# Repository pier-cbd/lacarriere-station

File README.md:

# Lacarriere Station 

## Specs
### Stage 1
- Powered by a battery recharged by a solar panel
- Three VGA cameras to take 360° photos
- Measures temperature/humidity/pressure with Bosch sensors
- Sends data via 2G+ network

### Stage 2
...

### Stage 3
...

## Sofwares
- KiCAD 7
- FreeCAD 0.20

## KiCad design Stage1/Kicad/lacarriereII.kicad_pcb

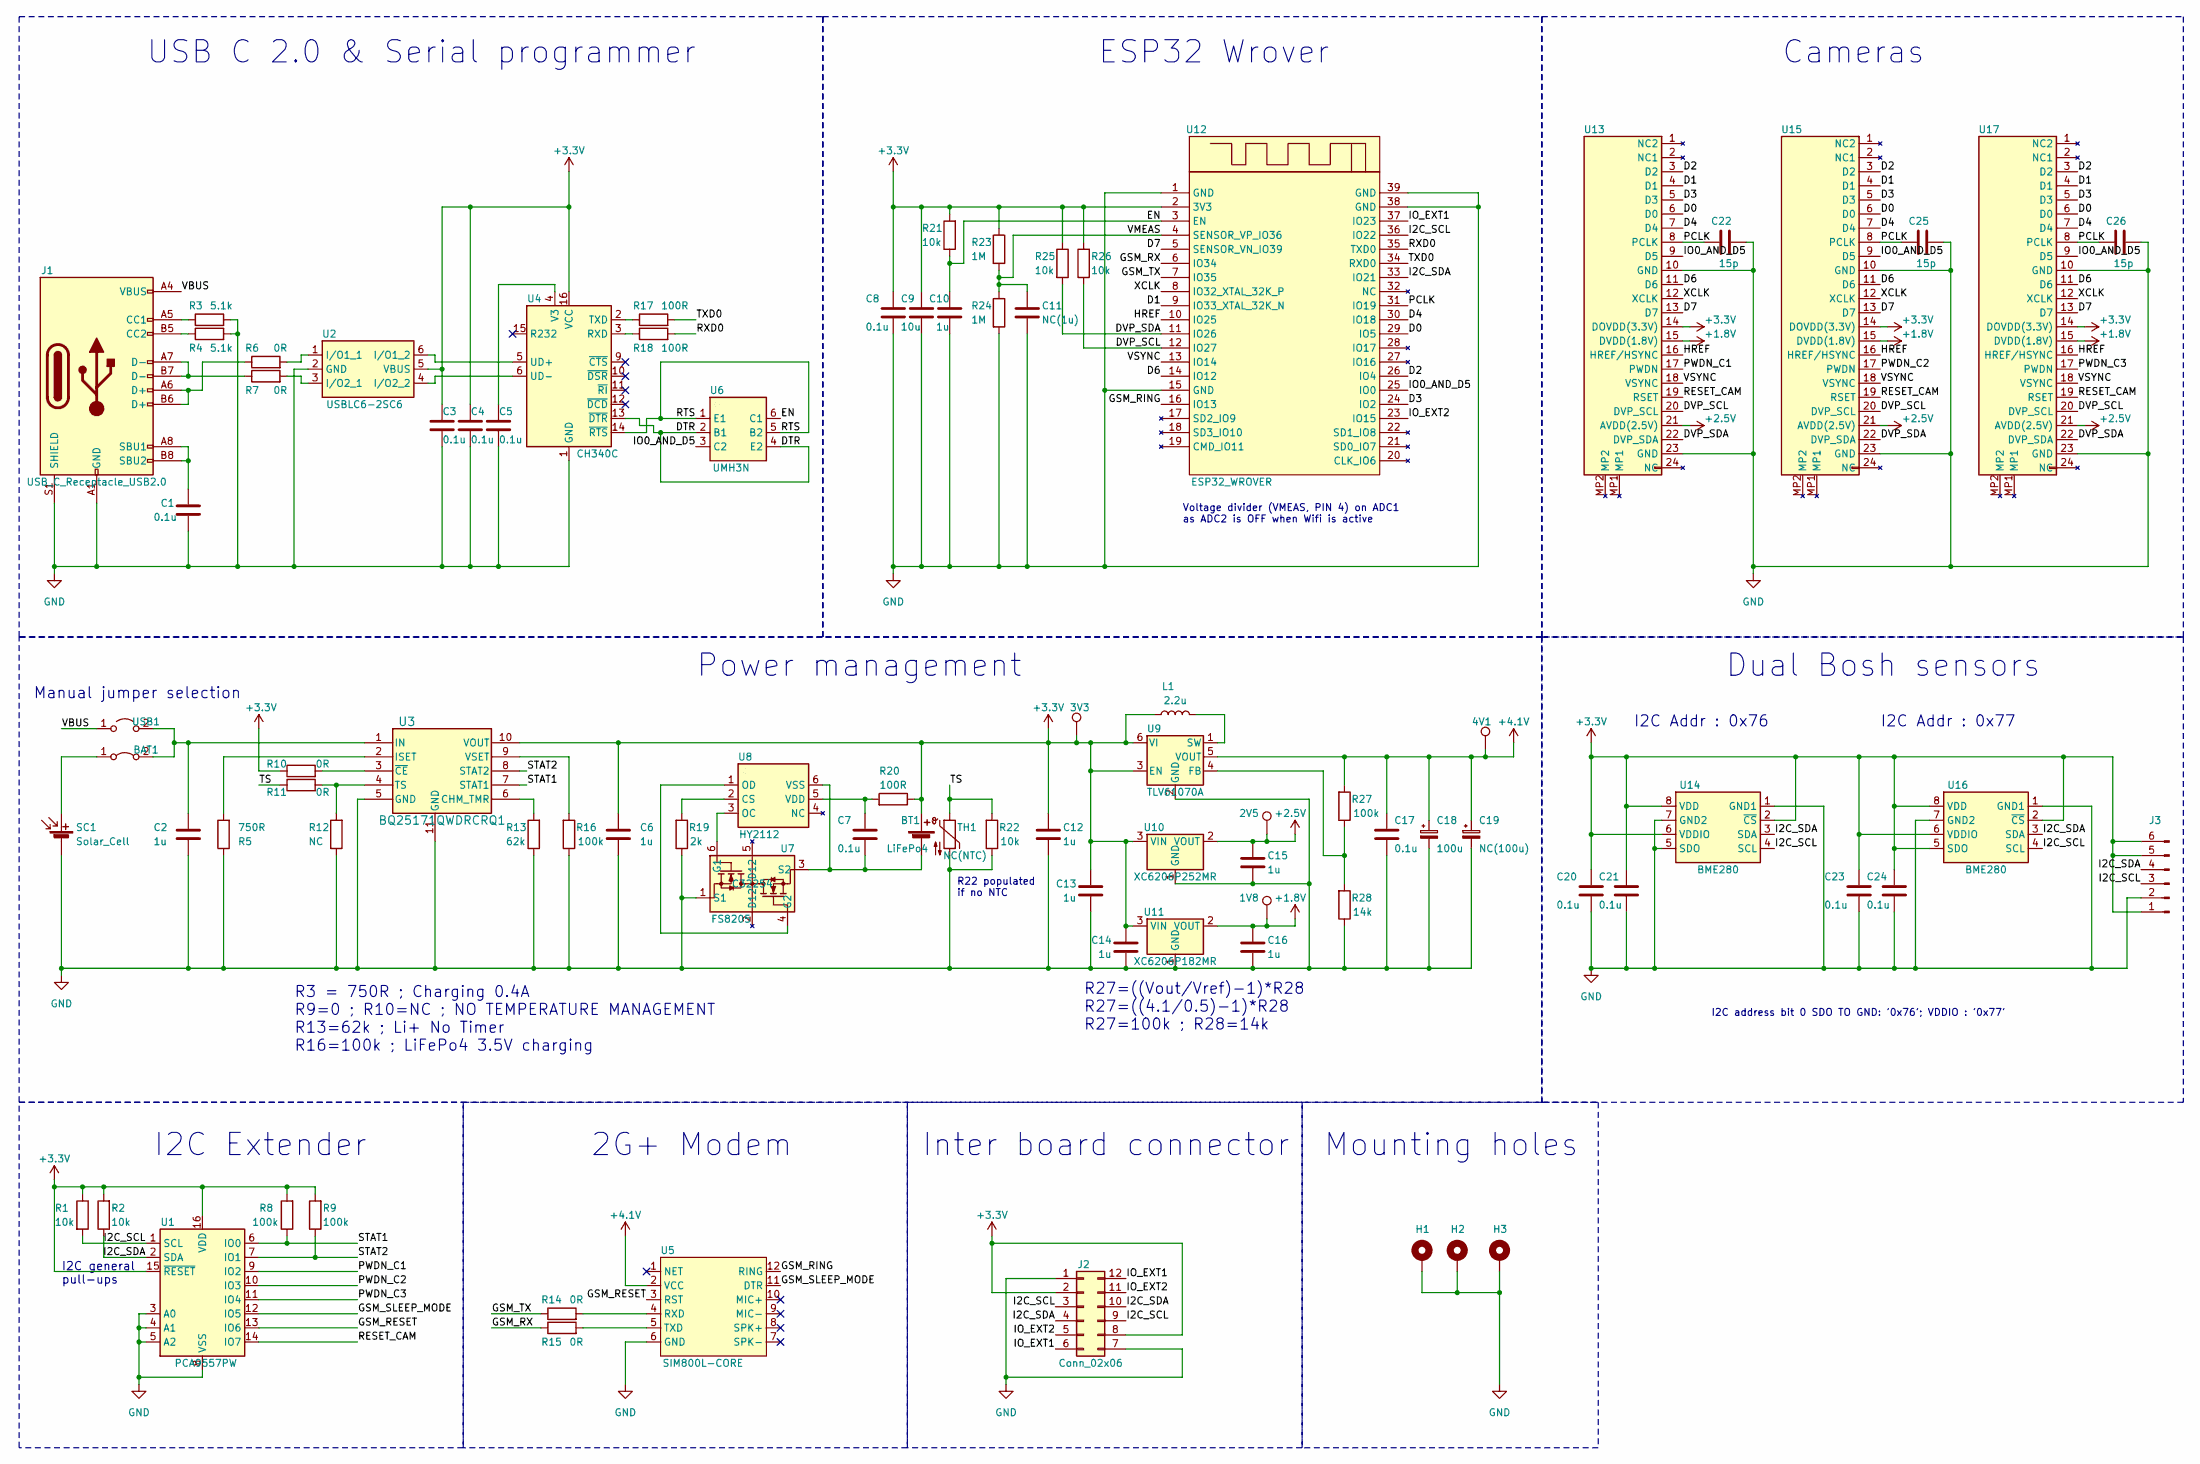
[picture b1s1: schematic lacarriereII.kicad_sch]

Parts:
1V8, 2V5, 3V3, 4V1: TestPoint; TestPoint_Pad_D1.5mm
BAT1: Jumper_2_Bridged; PinSocket_1x02_P2.54mm_Vertical_SMD_Pin1Right
BT1: LiFePo4; SolderWire-2.5sqmm_1x02_P8.8mm_D2.4mm_OD4.4mm
C1, C3, C4, C5, C7, C8, C17, C20, C21, C23, C24: 0.1u; C_0805_2012Metric_Pad1.18x1.45mm_HandSolder; LCSC C1711
C2, C6, C10, C12, C13, C14, C15, C16: 1u; C_0805_2012Metric_Pad1.18x1.45mm_HandSolder; LCSC C28323
C9: 10u; C_0805_2012Metric_Pad1.18x1.45mm_HandSolder; LCSC C15850
C11: NC(1u); C_0805_2012Metric_Pad1.18x1.45mm_HandSolder; LCSC C28323
C18: 100u; CP_EIA-7343-31_Kemet-D_Pad2.25x2.55mm_HandSolder; LCSC C110548
C19: NC(100u); CP_EIA-7343-31_Kemet-D_Pad2.25x2.55mm_HandSolder; LCSC C110548
C22, C25, C26: 15p; C_0805_2012Metric_Pad1.18x1.45mm_HandSolder; LCSC C1794
H1, H2, H3: MountingHole_Pad; MountingHole_3.2mm_M3_Pad_Via
J1: USB_C_Receptacle_USB2.0; USB_C_Receptacle_HRO_TYPE-C-31-M-12
J2: Conn_02x06; CENTRAL-HEADER
J3: Conn_01x06_Pin; PinHeader_1x06_P2.54mm_Vertical
L1: 2.2u; XEL4030222MEC
R1, R2, R21, R22, R25, R26: 10k; R_0805_2012Metric_Pad1.20x1.40mm_HandSolder
R3, R4: 5.1k; R_0805_2012Metric_Pad1.20x1.40mm_HandSolder
R5: 750R; R_0805_2012Metric_Pad1.20x1.40mm_HandSolder
R6, R7, R10, R11, R14, R15: 0R; R_0805_2012Metric_Pad1.20x1.40mm_HandSolder
R8, R9, R16, R27: 100k; R_0805_2012Metric_Pad1.20x1.40mm_HandSolder
R12: NC; R_0805_2012Metric_Pad1.20x1.40mm_HandSolder
R13: 62k; R_0805_2012Metric_Pad1.20x1.40mm_HandSolder
R17, R18, R20: 100R; R_0805_2012Metric_Pad1.20x1.40mm_HandSolder
R19: 2k; R_0805_2012Metric_Pad1.20x1.40mm_HandSolder
R23, R24: 1M; R_0805_2012Metric_Pad1.20x1.40mm_HandSolder
R28: 14k; R_0805_2012Metric_Pad1.20x1.40mm_HandSolder; LCSC C17464
SC1: Solar_Cell; SolderWire-2.5sqmm_1x02_P8.8mm_D2.4mm_OD4.4mm
TH1: NC(NTC); PinHeader_1x02_P2.54mm_Vertical
U1: PCA9557PW; TSSOP-16_4.4x5mm_P0.65mm
U2: USBLC6-2SC6; SOT-23-6_Handsoldering; Mouser Part Number 511-USBLC6-2SC6
U3: BQ25171QWDRCRQ1; VSON10_BQ25171_3X3_TEX-M
U4: CH340C; SOIC-16_3.9x9.9mm_P1.27mm
U5: SIM800L-CORE
U6: UMH3N; SOT-363_SC-70-6; LCSC C123008
U7: FS8205; SOT-23-6_Handsoldering; LCSC C32254
U8: HY2112; SOT-23-6_Handsoldering; LCSC C168763
U9: TLV61070A; SOT-23-6_Handsoldering; LCSC C6881375
U10: XC6206P252MR; SOT-23-3; LCSC C2934870
U11: XC6206P182MR; SOT-23-3; LCSC C424700
U12: ESP32_WROVER; ESP32-WROVER
U13, U15, U17: F34G1A7Q1E8C24
U14, U16: BME280; Bosch_LGA-8_2.5x2.5mm_P0.65mm_ClockwisePinNumbering
USB1: Jumper_2_Open; PinSocket_1x02_P2.54mm_Vertical_SMD_Pin1Right

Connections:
+1V2: 1V8.1, C16.1, U11.2 (VOUT), U13.15 (DVDD(1.8V)), U15.15 (DVDD(1.8V)), U17.15 (DVDD(1.8V))
+2V8: 2V5.1, C15.1, U10.2 (VOUT), U13.21 (AVDD(2.5V)), U15.21 (AVDD(2.5V)), U17.21 (AVDD(2.5V))
+3.3V: 3V3.1, BT1.1 (+), C3.1, C4.1, C6.1, C8.1, C9.1, C12.1, C13.1, C14.1, C20.1, C21.1, C23.1, C24.1, J2.2, J2.8, J3.1, J3.5, J3.6, L1.1, R1.1, R2.2, R8.2, R9.2, R10.1, R20.1, R21.2, R23.1, R25.1, R26.2, U1.15 (~RESET), U1.16 (VDD), U2.5 (VBUS), U3.10 (VOUT), U4.16 (VCC), U9.3 (EN), U9.6 (VI), U10.3 (VIN), U11.3 (VIN), U12.2 (3V3), U13.14 (DOVDD(3.3V)), U14.2 (~CS), U14.6 (VDDIO), U14.8 (VDD), U15.14 (DOVDD(3.3V)), U16.2 (~CS), U16.5 (SDO), U16.6 (VDDIO), U16.8 (VDD), U17.14 (DOVDD(3.3V)); also elsewhere on the board
+4V: 4V1.1, C17.1, C18.1, C19.1, R27.2, U5.2 (VCC), U9.5 (VOUT)
/D0: U12.29 (IO5), U13.6 (D0), U15.6 (D0), U17.6 (D0)
/D1: U12.9 (IO33_XTAL_32K_N), U13.4 (D1), U15.4 (D1), U17.4 (D1)
/D2: U12.26 (IO4), U13.3 (D2), U15.3 (D2), U17.3 (D2)
/D3: U12.24 (IO2), U13.5 (D3), U15.5 (D3), U17.5 (D3)
/D4: U12.30 (IO18), U13.7 (D4), U15.7 (D4), U17.7 (D4)
/D6: U12.14 (IO12), U13.11 (D6), U15.11 (D6), U17.11 (D6)
/D7: U12.5 (SENSOR_VN_IO39), U13.13 (D7), U15.13 (D7), U17.13 (D7)
/DTR: U4.13 (~DTR), U6.2 (B1), U6.4 (E2)
/DVP_SCL: R26.1, U12.12 (IO27), U13.20 (DVP_SCL), U15.20 (DVP_SCL), U17.20 (DVP_SCL)
/DVP_SDA: R25.2, U12.11 (IO26), U13.22 (DVP_SDA), U15.22 (DVP_SDA), U17.22 (DVP_SDA)
/EN: C10.1, R21.1, U6.6 (C1), U12.3 (EN)
/GSM_RESET: U1.13 (IO6), U5.3 (RST)
/GSM_RING: U5.12 (RING), U12.16 (IO13)
/GSM_RX: R15.1, U12.6 (IO34)
/GSM_SLEEP_MODE: U1.12 (IO5), U5.11 (DTR)
/GSM_TX: R14.1, U12.7 (IO35)
/HREF: U12.10 (IO25), U13.16 (HREF/HSYNC), U15.16 (HREF/HSYNC), U17.16 (HREF/HSYNC)
/I2C_SCL: J2.3, J2.9, J3.3, R1.2, U1.1 (SCL), U12.36 (IO22), U14.4 (SCL), U16.4 (SCL)
/I2C_SDA: J2.4, J2.10, J3.4, R2.1, U1.2 (SDA), U12.33 (IO21), U14.3 (SDA), U16.3 (SDA)
/IO0_AND_D5: U6.3 (C2), U12.25 (IO0), U13.9 (D5), U15.9 (D5), U17.9 (D5)
/IO_EXT1: J2.6, J2.12, U12.37 (IO23)
/IO_EXT2: J2.5, J2.11, U12.23 (IO15)
/PCLK: C22.1, C25.1, C26.1, U12.31 (IO19), U13.8 (PCLK), U15.8 (PCLK), U17.8 (PCLK)
/PWDN_C1: U1.9 (IO2), U13.17 (PWDN)
/PWDN_C2: U1.10 (IO3), U15.17 (PWDN)
/PWDN_C3: U1.11 (IO4), U17.17 (PWDN)
/RESET_CAM: U1.14 (IO7), U13.19 (RSET), U15.19 (RSET), U17.19 (RSET)
/RTS: U4.14 (~RTS), U6.1 (E1), U6.5 (B2)
/RXD0: R18.2, U12.35 (TXD0)
/STAT1: R8.1, U1.6 (IO0), U3.7 (STAT1)
/STAT2: R9.1, U1.7 (IO1), U3.8 (STAT2)
/TS: R11.1, R22.2, TH1.1
/TXD0: R17.2, U12.34 (RXD0)
/VBUS: J1.A4 (VBUS), J1.A9 (VBUS), J1.B4 (VBUS), J1.B9 (VBUS), USB1.1 (A)
/VMEAS: C11.1, R23.2, R24.1, U12.4 (SENSOR_VP_IO36)
/VSYNC: U12.13 (IO14), U13.18 (VSYNC), U15.18 (VSYNC), U17.18 (VSYNC)
/XCLK: U12.8 (IO32_XTAL_32K_P), U13.12 (XCLK), U15.12 (XCLK), U17.12 (XCLK)
GND: C1.2, C2.2, C3.2, C4.2, C5.2, C6.2, C8.2, C9.2, C10.2, C11.2, C12.2, C13.2, C14.2, C15.2, C16.2, C17.2, C18.2, C19.2, C20.2, C21.2, C22.2, C23.2, C24.2, C25.2, C26.2, H1.1, H2.1, H3.1, J1.A1 (GND), J1.A12 (GND), J1.B1 (GND), J1.B12 (GND), J1.S1 (SHIELD), J2.1, J2.7, J3.2, R3.2, R4.2, R5.1, R12.1, R13.1, R16.1, R19.1, R22.1, R24.2, R28.1, SC1.2 (-), TH1.2, U1.3 (A0), U1.4 (A1), U1.5 (A2), U1.8 (VSS), U2.2 (GND), U3.5 (GND), U3.11 (GND), U4.1 (GND), U5.6 (GND), U7.1 (S1), U9.2 (GND), U10.1 (GND), U11.1 (GND), U12.1 (GND), U12.15 (GND), U12.38 (GND), U12.39 (GND), U13.10 (GND), U13.23 (GND), U14.1 (GND1), U14.5 (SDO), U14.7 (GND2), U15.10 (GND), U15.23 (GND), U16.1 (GND1), U16.7 (GND2), U17.10 (GND), U17.23 (GND); also elsewhere on the board
unnamed 42: BAT1.1 (A), SC1.1 (+); also elsewhere on the board
unnamed: BAT1.2 (B), C2.1, U3.1 (IN), USB1.2 (B)
unnamed 44: BT1.2 (-), C7.2, U7.3 (S2), U8.6 (VSS); also elsewhere on the board
unnamed: J1.A5 (CC1), R3.1
unnamed: J1.B5 (CC2), R4.1
unnamed: J1.A6 (D+), J1.B6 (D+), R6.1
unnamed: J1.A7 (D-), J1.B7 (D-), R7.1
unnamed: C1.1, J1.A8 (SBU1), J1.B8 (SBU2)
unnamed: R6.2, U2.1 (I/O1_1)
unnamed: U2.6 (I/O1_2), U4.5 (UD+)
unnamed: R7.2, U2.3 (I/O2_1)
unnamed: U2.4 (I/O2_2), U4.6 (UD-)
unnamed: R13.2, U3.6 (CHM_TMR)
unnamed: R5.2, U3.2 (ISET)
unnamed: R11.2, R12.2, U3.4 (TS)
unnamed: R16.2, U3.9 (VSET)
unnamed: R10.2, U3.3 (~CE)
unnamed: R18.1, U4.3 (RXD)
unnamed: R17.1, U4.2 (TXD)
unnamed: C5.1, U4.4 (V3)
unnamed: R14.2, U5.4 (RXD)
unnamed: R15.2, U5.5 (TXD)
unnamed: U7.6 (G1), U8.3 (OC)
unnamed: U7.4 (G2), U8.1 (OD)
unnamed: R19.2, U8.2 (CS)
unnamed: C7.1, R20.2, U8.5 (VDD)
unnamed: R27.1, R28.2, U9.4 (FB)
unnamed: L1.2, U9.1 (SW)

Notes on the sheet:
Inter board connector
I2C Extender
I2C address bit 0 SDO TO GND: '0x76'; VDDIO : '0x77'
I2C Addr : 0x76
2G+ Modem
Dual Bosh sensors
R22 populated if no NTC
I2C Addr : 0x77
Manual jumper selection
Mounting holes
I2C general pull-ups
Cameras
R27=((Vout/Vref)-1)*R28 R27=((4.1/0.5)-1)*R28 R27=100k ; R28=14k
R3 = 750R ; Charging 0.4A R9=0 ; R10=NC ; NO TEMPERATURE MANAGEMENT R13=62k ; Li+ No Timer R16=100k ; LiFePo4 3.5V charging
ESP32 Wrover
USB C 2.0 & Serial programmer
Power management
Voltage divider (VMEAS, PIN 4) on ADC1 as ADC2 is OFF when Wifi is active

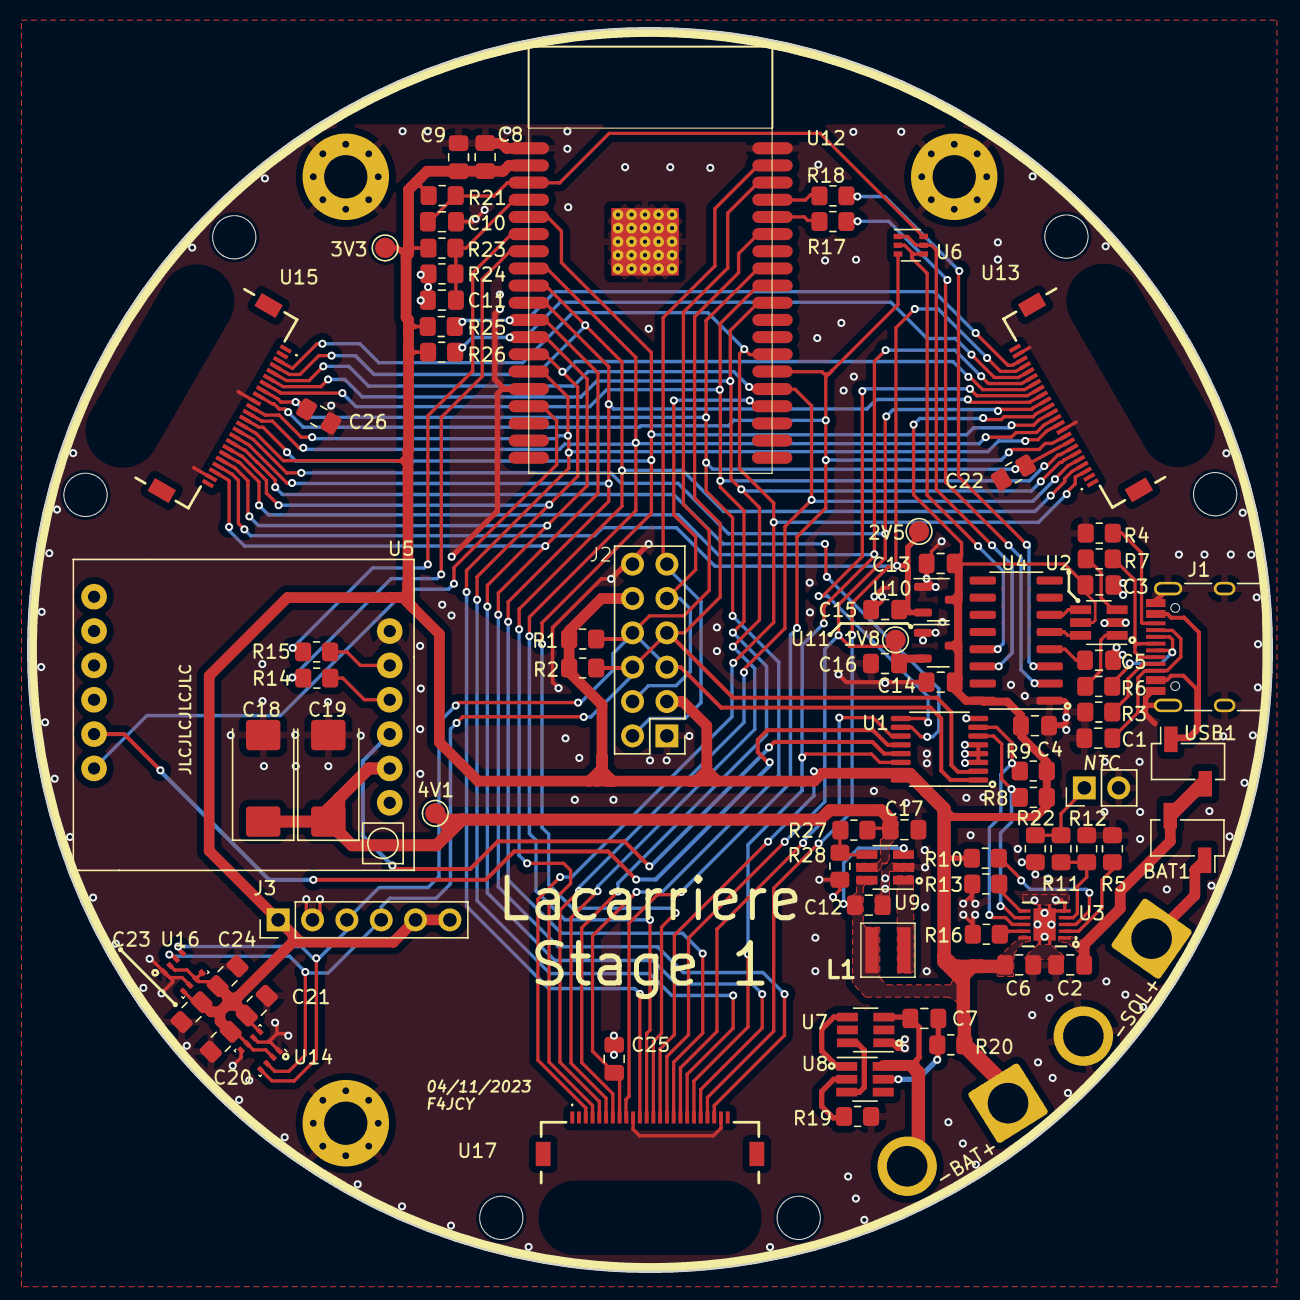
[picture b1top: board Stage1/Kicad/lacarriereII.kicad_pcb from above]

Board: 2 copper layers, 92.0 x 92.0 mm, 87 parts (0 on the bottom side), 70 nets.

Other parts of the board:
-BAT+: LiFePo4; SolderWire-2.5sqmm_1x02_P8.8mm_D2.4mm_OD4.4mm
-SOL+: Solar_Cell; SolderWire-2.5sqmm_1x02_P8.8mm_D2.4mm_OD4.4mm

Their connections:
+3.3V: -BAT+.1 (+); also elsewhere on the board
GND: -SOL+.2 (-); also elsewhere on the board
unnamed 42: -SOL+.1 (+); also elsewhere on the board
unnamed 44: -BAT+.2 (-); also elsewhere on the board

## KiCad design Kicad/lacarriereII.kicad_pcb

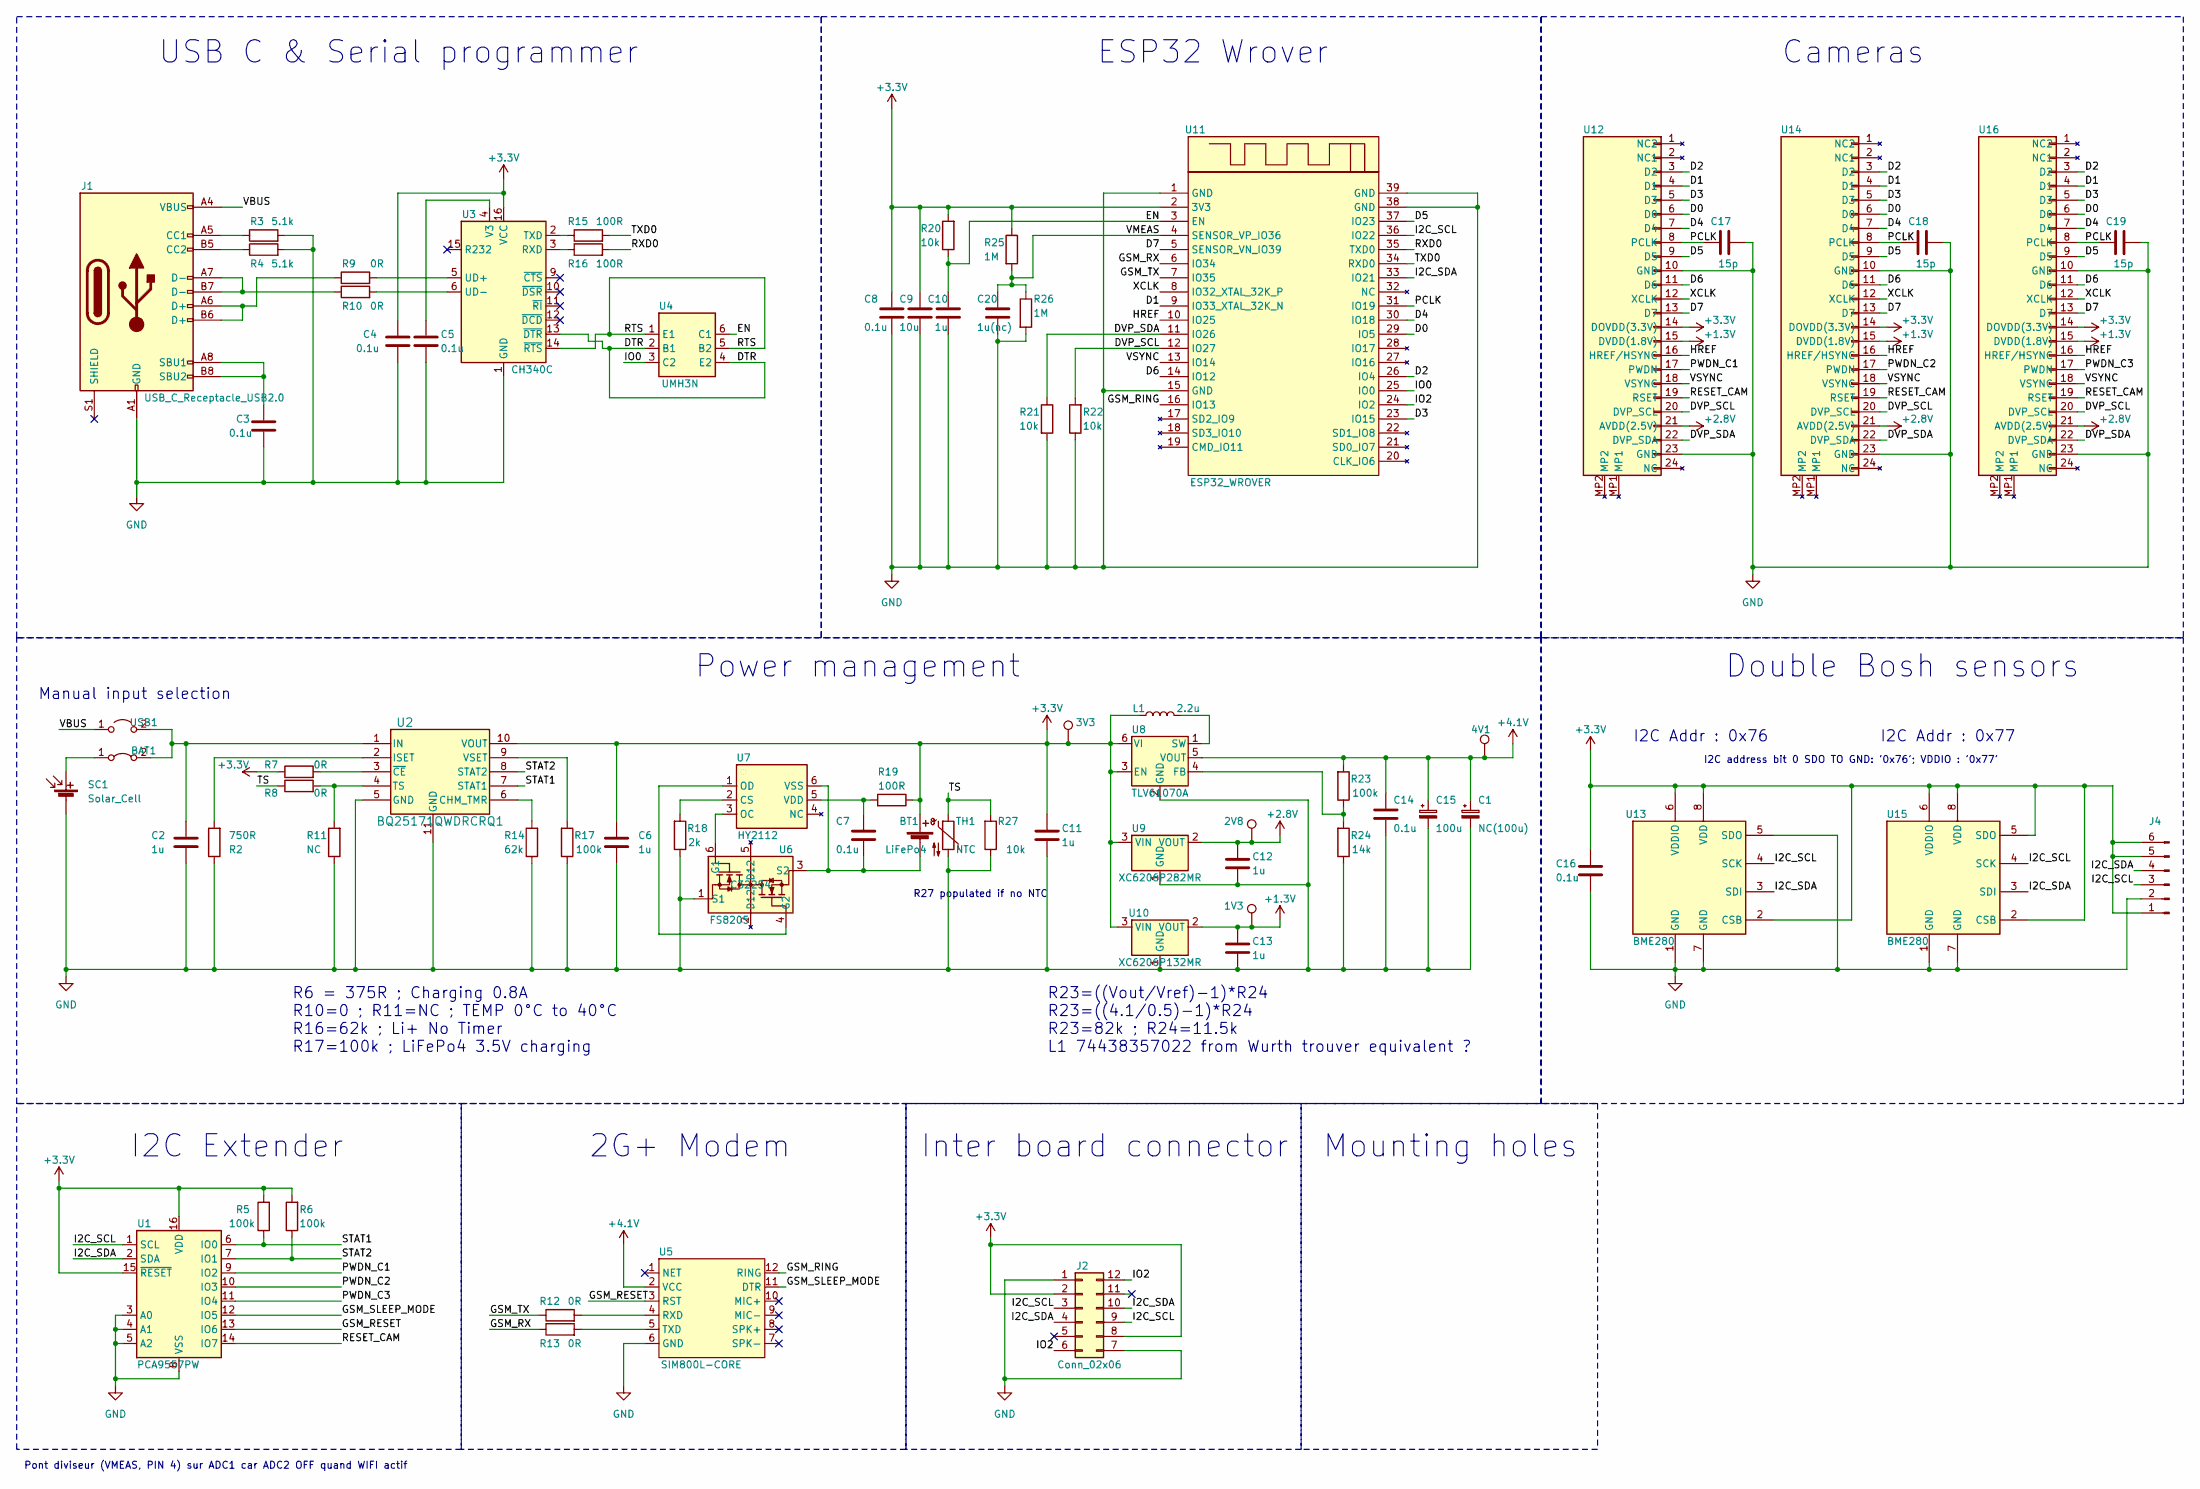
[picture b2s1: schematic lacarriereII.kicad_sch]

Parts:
1V3, 2V8, 3V3, 4V1: TestPoint; TestPoint_Pad_D1.5mm
BAT1: Jumper_2_Bridged; PinSocket_1x02_P2.54mm_Vertical_SMD_Pin1Right
BT1: LiFePo4; SolderWire-2.5sqmm_1x02_P8.8mm_D2.4mm_OD4.4mm
C1: NC(100u); CP_EIA-7343-31_Kemet-D_Pad2.25x2.55mm_HandSolder; LCSC C110548
C2, C6, C10, C11, C12, C13: 1u; C_0805_2012Metric_Pad1.18x1.45mm_HandSolder; LCSC C28323
C3, C4, C5, C7, C8, C14, C16: 0.1u; C_0805_2012Metric_Pad1.18x1.45mm_HandSolder; LCSC C1711
C9: 10u; C_0805_2012Metric_Pad1.18x1.45mm_HandSolder; LCSC C15850
C15: 100u; CP_EIA-7343-31_Kemet-D_Pad2.25x2.55mm_HandSolder; LCSC C110548
C17, C18, C19: 15p; C_0805_2012Metric_Pad1.18x1.45mm_HandSolder; LCSC C1794
C20: 1u(nc); C_0805_2012Metric_Pad1.18x1.45mm_HandSolder; LCSC C28323
J1: USB_C_Receptacle_USB2.0; USB_C_Receptacle_HRO_TYPE-C-31-M-12
J2: Conn_02x06; CENTRAL-HEADER
J4: Conn_01x06_Pin; PinHeader_1x06_P2.54mm_Vertical
L1: 2.2u; XEL4030222MEC
R2: 750R; R_0805_2012Metric_Pad1.20x1.40mm_HandSolder
R3, R4: 5.1k; R_0805_2012Metric_Pad1.20x1.40mm_HandSolder
R5, R6, R17, R23: 100k; R_0805_2012Metric_Pad1.20x1.40mm_HandSolder
R7, R8, R9, R10, R12, R13: 0R; R_0805_2012Metric_Pad1.20x1.40mm_HandSolder
R11: NC; R_0805_2012Metric_Pad1.20x1.40mm_HandSolder
R14: 62k; R_0805_2012Metric_Pad1.20x1.40mm_HandSolder
R15, R16, R19: 100R; R_0805_2012Metric_Pad1.20x1.40mm_HandSolder
R18: 2k; R_0805_2012Metric_Pad1.20x1.40mm_HandSolder
R20, R21, R22, R27: 10k; R_0805_2012Metric_Pad1.20x1.40mm_HandSolder
R24: 14k; R_0805_2012Metric_Pad1.20x1.40mm_HandSolder; LCSC C17464
R25, R26: 1M; R_0805_2012Metric_Pad1.20x1.40mm_HandSolder
SC1: Solar_Cell; SolderWire-2.5sqmm_1x02_P8.8mm_D2.4mm_OD4.4mm
TH1: NTC; PinHeader_1x02_P2.54mm_Vertical
U1: PCA9557PW; TSSOP-16_4.4x5mm_P0.65mm
U2: BQ25171QWDRCRQ1; VSON10_BQ25171_3X3_TEX-M
U3: CH340C; SOIC-16_3.9x9.9mm_P1.27mm
U4: UMH3N; SOT-363_SC-70-6; LCSC C123008
U5: SIM800L-CORE
U6: FS8205; SOT-23-6_Handsoldering; LCSC C32254
U7: HY2112; SOT-23-6_Handsoldering; LCSC C168763
U8: TLV61070A; SOT-23-6_Handsoldering; LCSC C6881375
U9: XC6206P282MR; SOT-23-3; LCSC C2934870
U10: XC6206P132MR; SOT-23-3; LCSC C424700
U11: ESP32_WROVER; ESP32-WROVER
U12, U14, U16: F34G1A7Q1E8C24
U13, U15: BME280; Bosch_LGA-8_2.5x2.5mm_P0.65mm_ClockwisePinNumbering
USB1: Jumper_2_Open; PinSocket_1x02_P2.54mm_Vertical_SMD_Pin1Right

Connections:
+1V2: 1V3.1, C13.1, U10.2 (VOUT), U12.15 (DVDD(1.8V)), U14.15 (DVDD(1.8V)), U16.15 (DVDD(1.8V))
+2V8: 2V8.1, C12.1, U9.2 (VOUT), U12.21 (AVDD(2.5V)), U14.21 (AVDD(2.5V)), U16.21 (AVDD(2.5V))
+3.3V: 3V3.1, BT1.1 (+), C4.1, C6.1, C8.1, C9.1, C11.1, C16.1, J2.2, J2.8, J4.1, J4.5, J4.6, L1.1, R5.2, R6.2, R7.1, R19.1, R20.2, R25.1, U1.15 (~RESET), U1.16 (VDD), U2.10 (VOUT), U3.16 (VCC), U8.3 (EN), U8.6 (VI), U9.3 (VIN), U10.3 (VIN), U11.2 (3V3), U12.14 (DOVDD(3.3V)), U13.2 (CSB), U13.6 (VDDIO), U13.8 (VDD), U14.14 (DOVDD(3.3V)), U15.2 (CSB), U15.5 (SDO), U15.6 (VDDIO), U15.8 (VDD), U16.14 (DOVDD(3.3V))
+4V: 4V1.1, C1.1, C14.1, C15.1, R23.2, U5.2 (VCC), U8.5 (VOUT)
/D0: U11.29 (IO5), U12.6 (D0), U14.6 (D0), U16.6 (D0)
/D1: U11.9 (IO33_XTAL_32K_N), U12.4 (D1), U14.4 (D1), U16.4 (D1)
/D2: U11.26 (IO4), U12.3 (D2), U14.3 (D2), U16.3 (D2)
/D3: U11.23 (IO15), U12.5 (D3), U14.5 (D3), U16.5 (D3)
/D4: U11.30 (IO18), U12.7 (D4), U14.7 (D4), U16.7 (D4)
/D5: U11.37 (IO23), U12.9 (D5), U14.9 (D5), U16.9 (D5)
/D6: U11.14 (IO12), U12.11 (D6), U14.11 (D6), U16.11 (D6)
/D7: U11.5 (SENSOR_VN_IO39), U12.13 (D7), U14.13 (D7), U16.13 (D7)
/DTR: U3.13 (~DTR), U4.2 (B1), U4.4 (E2)
/DVP_SCL: R22.2, U11.12 (IO27), U12.20 (DVP_SCL), U14.20 (DVP_SCL), U16.20 (DVP_SCL)
/DVP_SDA: R21.1, U11.11 (IO26), U12.22 (DVP_SDA), U14.22 (DVP_SDA), U16.22 (DVP_SDA)
/EN: C10.1, R20.1, U4.6 (C1), U11.3 (EN)
/GSM_RESET: U1.13 (IO6), U5.3 (RST)
/GSM_RING: U5.12 (RING), U11.16 (IO13)
/GSM_RX: R13.1, U11.6 (IO34)
/GSM_SLEEP_MODE: U1.12 (IO5), U5.11 (DTR)
/GSM_TX: R12.1, U11.7 (IO35)
/HREF: U11.10 (IO25), U12.16 (HREF/HSYNC), U14.16 (HREF/HSYNC), U16.16 (HREF/HSYNC)
/I2C_SCL: J2.3, J2.9, J4.3, U1.1 (SCL), U11.36 (IO22), U13.4 (SCK), U15.4 (SCK)
/I2C_SDA: J2.4, J2.10, J4.4, U1.2 (SDA), U11.33 (IO21), U13.3 (SDI), U15.3 (SDI)
/IO0: U4.3 (C2), U11.25 (IO0)
/IO2: J2.6, J2.12, U11.24 (IO2)
/PCLK: C17.1, C18.1, C19.1, U11.31 (IO19), U12.8 (PCLK), U14.8 (PCLK), U16.8 (PCLK)
/PWDN_C1: U1.9 (IO2), U12.17 (PWDN)
/PWDN_C2: U1.10 (IO3), U14.17 (PWDN)
/PWDN_C3: U1.11 (IO4), U16.17 (PWDN)
/RESET_CAM: U1.14 (IO7), U12.19 (RSET), U14.19 (RSET), U16.19 (RSET)
/RTS: U3.14 (~RTS), U4.1 (E1), U4.5 (B2)
/RXD0: R16.2, U11.35 (TXD0)
/STAT1: R5.1, U1.6 (IO0), U2.7 (STAT1)
/STAT2: R6.1, U1.7 (IO1), U2.8 (STAT2)
/TS: R8.1, R27.2, TH1.1
/TXD0: R15.2, U11.34 (RXD0)
/VBUS: J1.A4 (VBUS), J1.A9 (VBUS), J1.B4 (VBUS), J1.B9 (VBUS), USB1.1 (A)
/VMEAS: C20.1, R25.2, R26.1, U11.4 (SENSOR_VP_IO36)
/VSYNC: U11.13 (IO14), U12.18 (VSYNC), U14.18 (VSYNC), U16.18 (VSYNC)
/XCLK: U11.8 (IO32_XTAL_32K_P), U12.12 (XCLK), U14.12 (XCLK), U16.12 (XCLK)
GND: C1.2, C2.2, C3.2, C4.2, C5.2, C6.2, C8.2, C9.2, C10.2, C11.2, C12.2, C13.2, C14.2, C15.2, C16.2, C17.2, C18.2, C19.2, C20.2, J1.A1 (GND), J1.A12 (GND), J1.B1 (GND), J1.B12 (GND), J2.1, J2.7, J4.2, R2.1, R3.2, R4.2, R11.1, R14.1, R17.1, R18.1, R21.2, R22.1, R24.1, R26.2, R27.1, SC1.2 (-), TH1.2, U1.3 (A0), U1.4 (A1), U1.5 (A2), U1.8 (VSS), U2.5 (GND), U2.11 (GND), U3.1 (GND), U5.6 (GND), U6.1 (S1), U8.2 (GND), U9.1 (GND), U10.1 (GND), U11.1 (GND), U11.15 (GND), U11.38 (GND), U11.39 (GND), U12.10 (GND), U12.23 (GND), U13.1 (GND), U13.5 (SDO), U13.7 (GND), U14.10 (GND), U14.23 (GND), U15.1 (GND), U15.7 (GND), U16.10 (GND), U16.23 (GND)
unnamed: BAT1.1 (A), SC1.1 (+)
unnamed: BAT1.2 (B), C2.1, U2.1 (IN), USB1.2 (B)
unnamed: BT1.2 (-), C7.2, U6.3 (S2), U7.6 (VSS)
unnamed: J1.A5 (CC1), R3.1
unnamed: J1.B5 (CC2), R4.1
unnamed: J1.A6 (D+), J1.B6 (D+), R9.1
unnamed: J1.A7 (D-), J1.B7 (D-), R10.1
unnamed: C3.1, J1.A8 (SBU1), J1.B8 (SBU2)
unnamed: R14.2, U2.6 (CHM_TMR)
unnamed: R2.2, U2.2 (ISET)
unnamed: R8.2, R11.2, U2.4 (TS)
unnamed: R17.2, U2.9 (VSET)
unnamed: R7.2, U2.3 (~CE)
unnamed: R16.1, U3.3 (RXD)
unnamed: R15.1, U3.2 (TXD)
unnamed: R9.2, U3.5 (UD+)
unnamed: R10.2, U3.6 (UD-)
unnamed: C5.1, U3.4 (V3)
unnamed: R12.2, U5.4 (RXD)
unnamed: R13.2, U5.5 (TXD)
unnamed: U6.6 (G1), U7.3 (OC)
unnamed: U6.4 (G2), U7.1 (OD)
unnamed: R18.2, U7.2 (CS)
unnamed: C7.1, R19.2, U7.5 (VDD)
unnamed: R23.1, R24.2, U8.4 (FB)
unnamed: L1.2, U8.1 (SW)

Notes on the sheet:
Inter board connector
I2C Extender
I2C address bit 0 SDO TO GND: '0x76'; VDDIO : '0x77'
I2C Addr : 0x76
2G+ Modem
Double Bosh sensors
R27 populated if no NTC
I2C Addr : 0x77
Manual input selection
Mounting holes
Cameras
R23=((Vout/Vref)-1)*R24 R23=((4.1/0.5)-1)*R24 R23=82k ; R24=11.5k L1 74438357022 from Wurth trouver equivalent ?
R6 = 375R ; Charging 0.8A R10=0 ; R11=NC ; TEMP 0°C to 40°C R16=62k ; Li+ No Timer R17=100k ; LiFePo4 3.5V charging
ESP32 Wrover
USB C & Serial programmer
Power management
Pont diviseur (VMEAS, PIN 4) sur ADC1 car ADC2 OFF quand WIFI actif

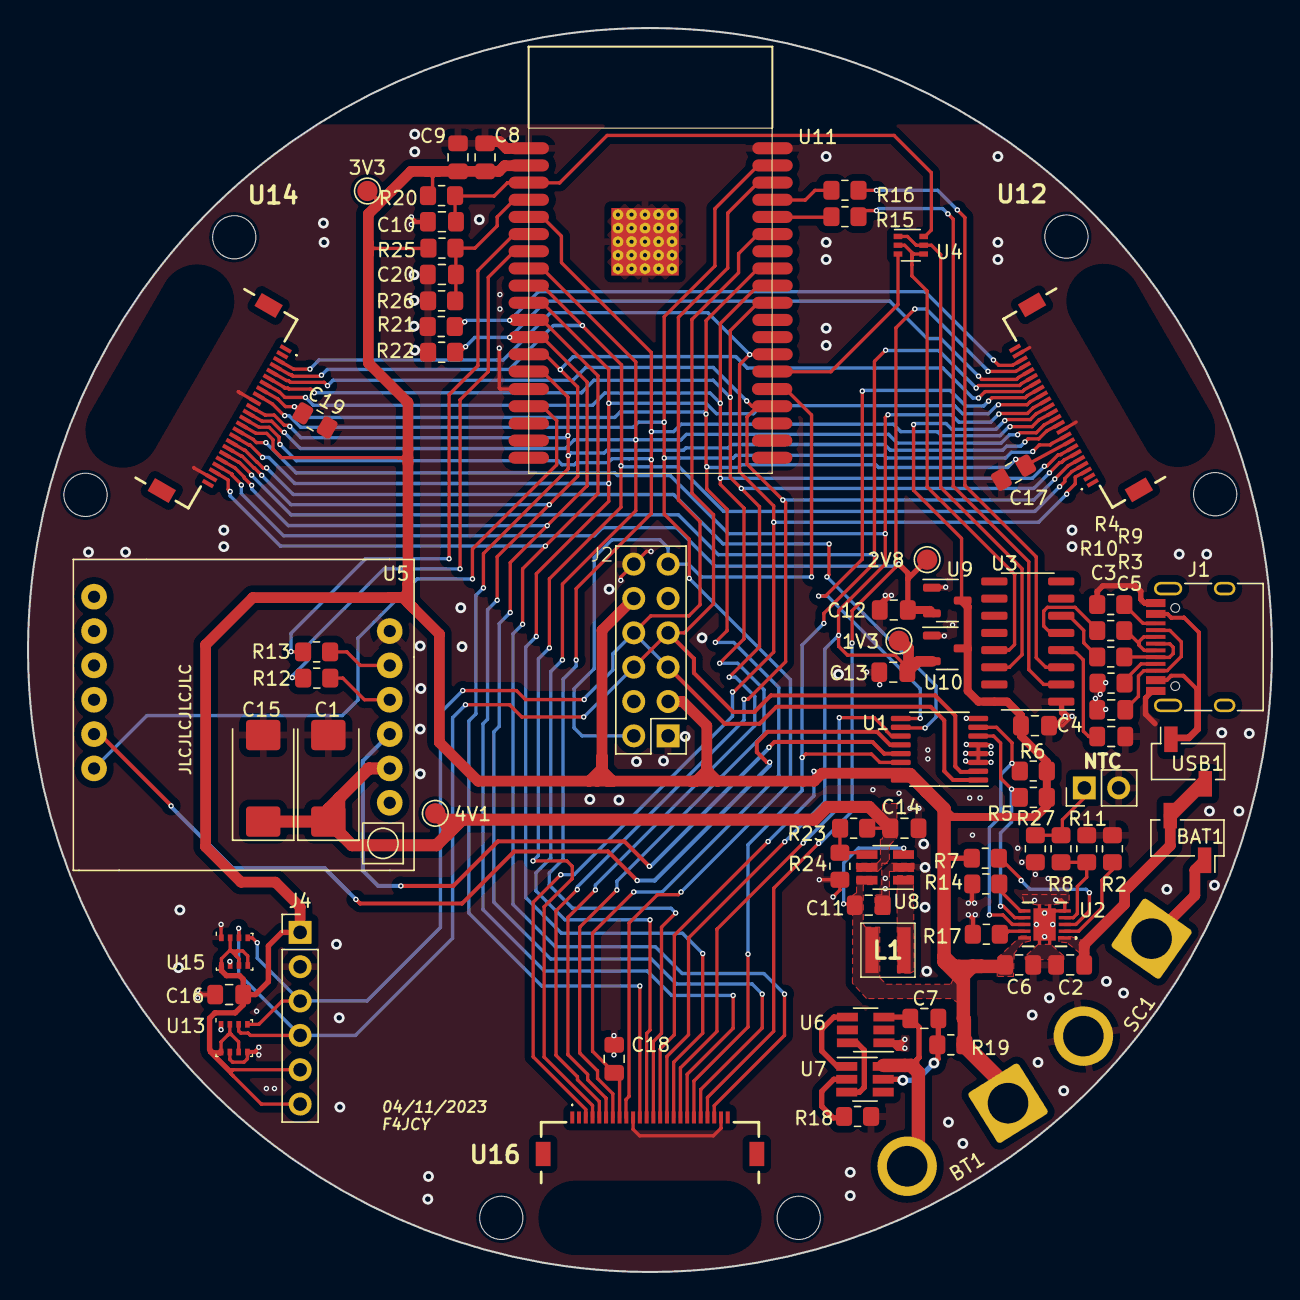
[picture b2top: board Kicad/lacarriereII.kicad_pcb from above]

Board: 2 copper layers, 92.0 x 92.0 mm, 75 parts (0 on the bottom side), 68 nets.

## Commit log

2023-11-04 [add] Kicad 7 project folder of the v2 board
2023-11-05 [change] ov2640 footprint and add BOM
2023-11-05 Update README.md
    [update] readme
2023-11-06 [refactor] folder structure
2023-11-07 [add] mounting holes + custom footprints lib
2023-11-08 [update] sourcing BOM + add main components datasheets
2023-11-09 [add] white border + stage1 image
2023-11-09 Update README.md
    [add] stage1 image
2023-11-17 [update] Stage1 schematic after olli's review
2023-11-17 [fix] a few mistakes on schematic ... ready to reroute!
2023-11-24 [reroute] pcb board after oli's review
2023-11-24 [update] sourcing file + minors component placements on pcb
2023-11-24 [change] via size to be compatible witch jlc capabilities specs
2023-11-27 [update] camera holder and Stage1 picture
